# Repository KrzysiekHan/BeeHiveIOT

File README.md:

# BeeHiveIOT
Beehive arduino device to send data with SMS and WebServer

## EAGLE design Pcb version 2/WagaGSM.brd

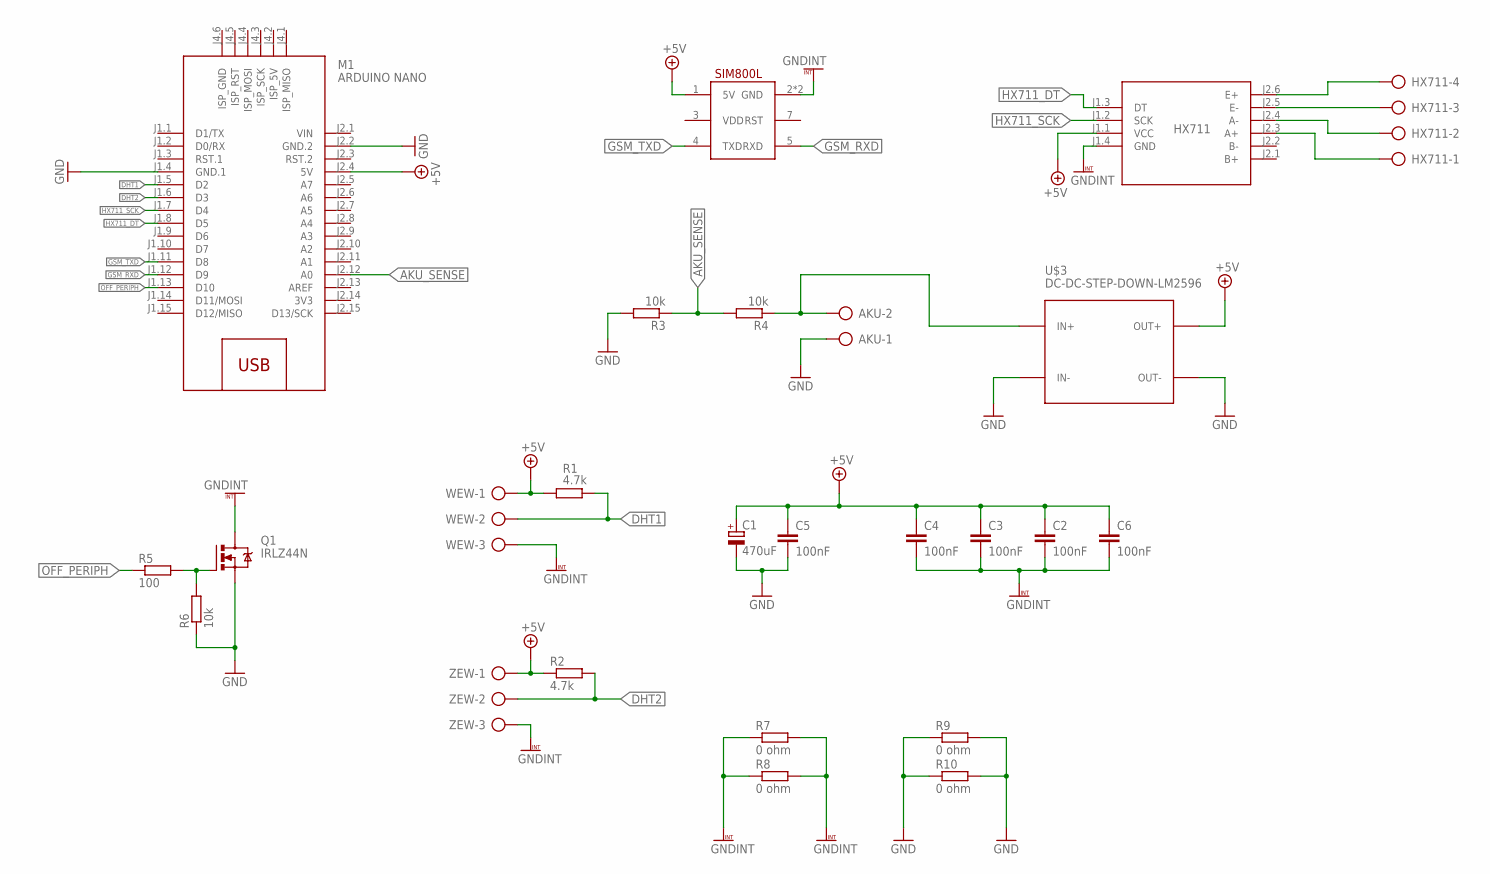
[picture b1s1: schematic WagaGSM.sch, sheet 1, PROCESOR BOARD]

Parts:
AKU: AK500/2-H
C1: 470uF; E5-10,5
C2, C3, C4, C5, C6: 100nF; C050-030X075
HX711: AK300/4
M1: ARDUINO NANO; ARDUINO-NANO-3.0#ISP
Q1: IRLZ44N; TO220BH
R1, R2: 4.7k; 0204/7
R3, R4: 10k; 0207/10
R5: 100; 0207/7
R6: 10k; 0207/7
R7, R8, R9, R10: 0 ohm; 0204/7
U$1: SIM800L; SIP
U$2: HX711
U$3: DC-DC-STEP-DOWN-LM2596
WEW: AK500/3-H
ZEW: AK500/3-H

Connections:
3V3: M1.J2.14 (3V3)
+5V: C1.+, C2.1, C3.1, C4.1, C5.1, C6.1, M1.J2.4 (5V), R1.1, R2.1, U$1.1 (5V), U$2.J1.1 (VCC), U$3.OUT+, WEW.1, ZEW.1
AKU_SENSE: M1.J2.12 (A0), R3.1, R4.2
B-: U$2.J2.2 (B-)
DHT1: M1.J1.5 (D2), R1.2, WEW.2
DHT2: M1.J1.6 (D3), R2.2, ZEW.2
GND: AKU.1, C1.-, C5.2, M1.J1.4 (GND.1), M1.J2.2 (GND.2), Q1.S, R3.2, R6.1, R9.1, R9.2, R10.1, R10.2, U$3.IN-, U$3.OUT-
GNDINT: C2.2, C3.2, C4.2, C6.2, Q1.D, R7.1, R7.2, R8.1, R8.2, U$1.2 (GND), U$1.6 (GND), U$2.J1.4 (GND), WEW.3, ZEW.3
GSM_RXD: M1.J1.12 (D9), U$1.5 (RXD)
GSM_TXD: M1.J1.11 (D8), U$1.4 (TXD)
HX711_DT: M1.J1.8 (D5), U$2.J1.3 (DT)
HX711_SCK: M1.J1.7 (D4), U$2.J1.2 (SCK)
unnamed: Q1.G, R5.2, R6.2
unnamed: AKU.2, R4.1, U$3.IN+
unnamed: HX711.4, U$2.J2.6 (E+)
unnamed: HX711.3, U$2.J2.5 (E-)
unnamed: HX711.2, U$2.J2.4 (A-)
unnamed: HX711.1, U$2.J2.3 (A+)
OFF_PERIPH: M1.J1.13 (D10), R5.1
VIN: M1.J2.1 (VIN)

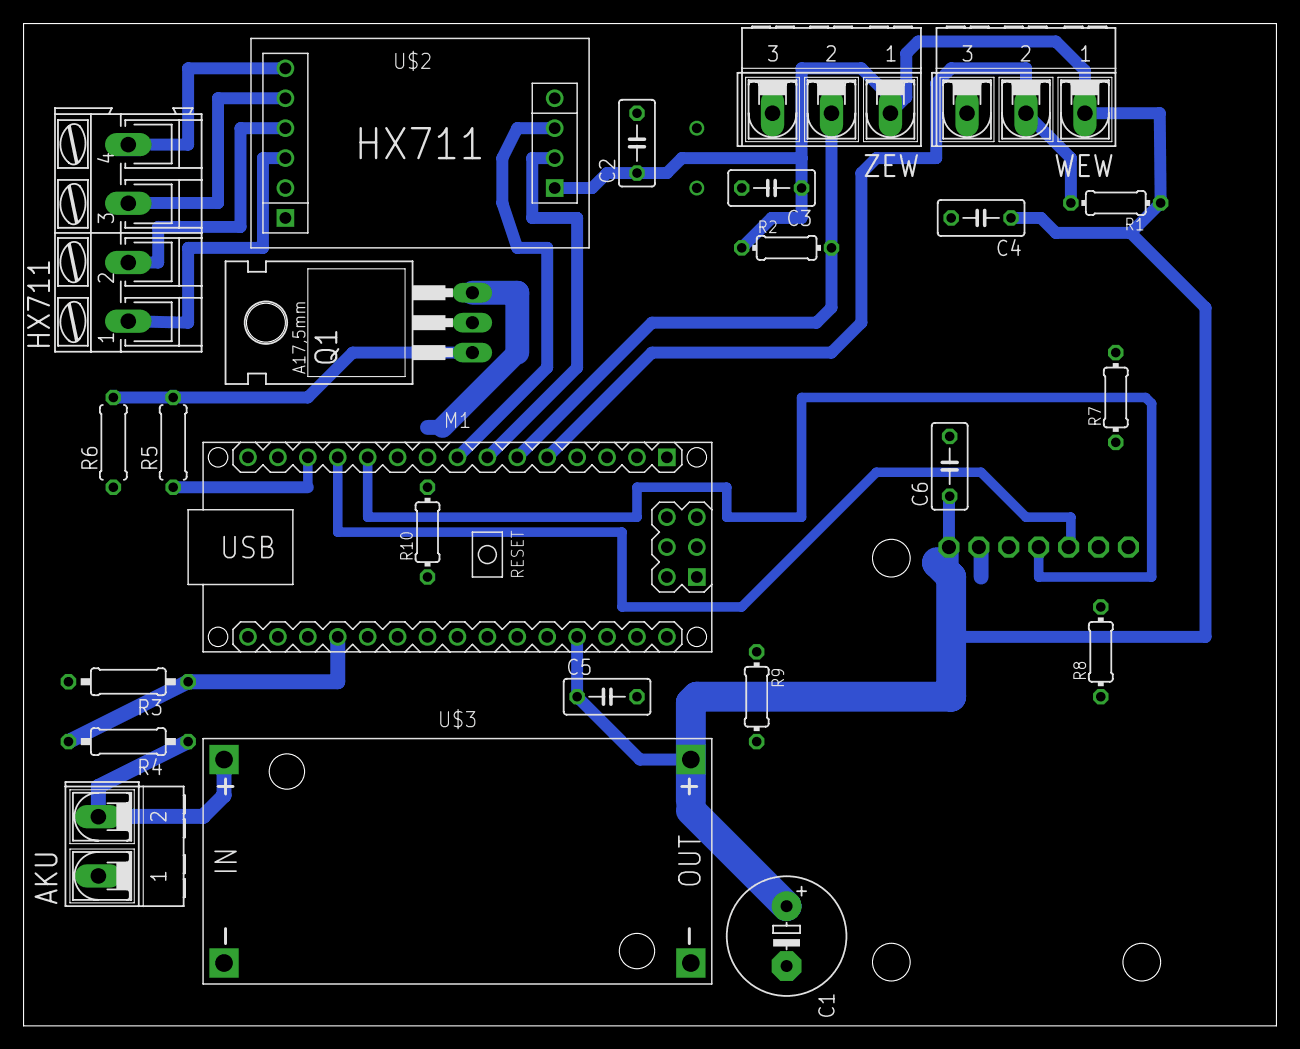
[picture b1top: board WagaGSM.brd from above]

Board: 2 copper layers, 106.3 x 85.1 mm, 25 parts (0 on the bottom side), 17 nets.

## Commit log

2018-08-10 pierwszy commit na gita
2018-08-10 przerobki na biblioteke barebone
2018-08-11 prace nad sekwencją
2018-08-11 sequence finished + scheduling + time + location
2018-08-11 korekta po zapisie
2018-08-11 HX711 library added to files
2018-08-11 libs
2018-08-11 config scale
2018-08-28 dodany reset programu
2018-12-31 dodane biblioteki i pcb
2019-01-13 RTC, New pcb, New sim800 lib
2019-01-29 new program version
2019-01-29 deleted old program, added RTC library

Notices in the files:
parts and their libraries:
000_diy-modules: Released under the Creative Commons Attribution 4.0 International License: http://creativecommons.org/licenses/by/4.0
